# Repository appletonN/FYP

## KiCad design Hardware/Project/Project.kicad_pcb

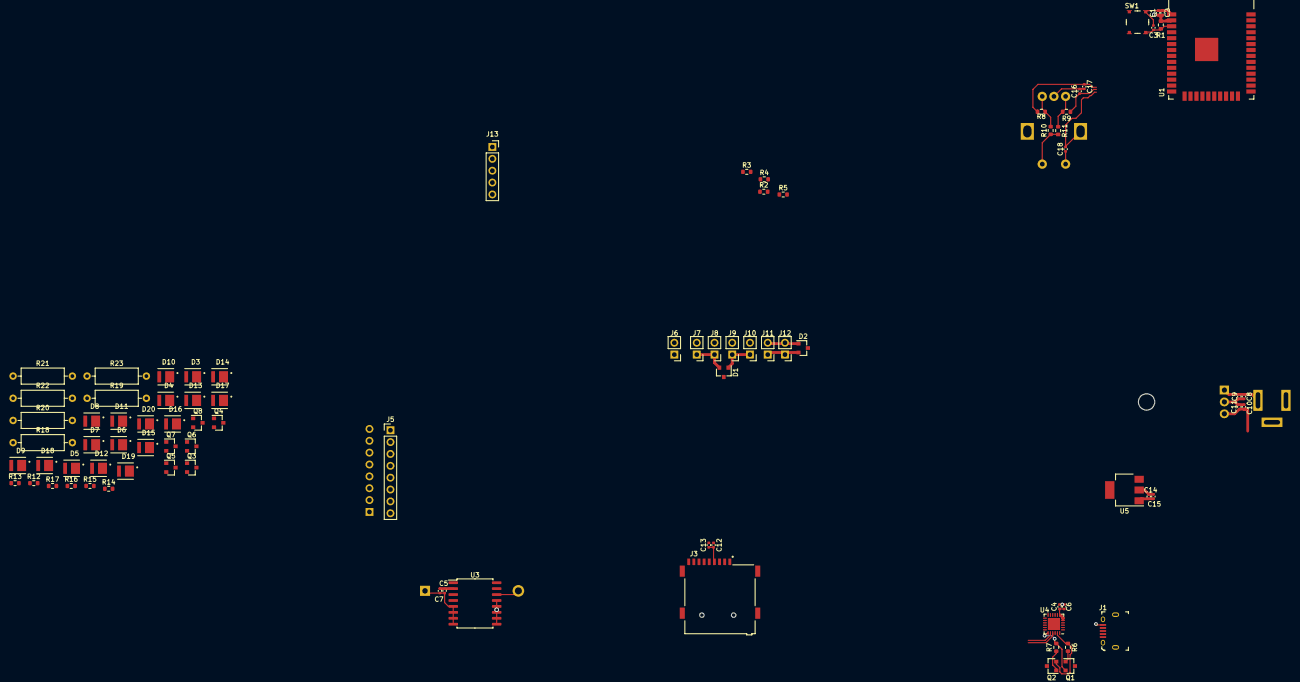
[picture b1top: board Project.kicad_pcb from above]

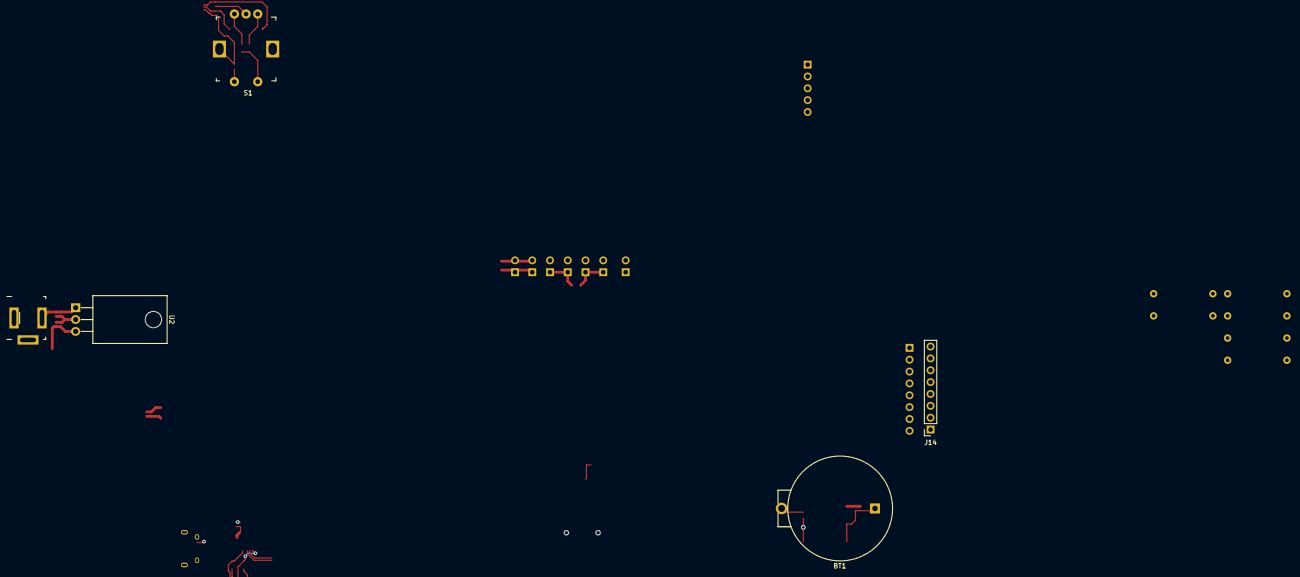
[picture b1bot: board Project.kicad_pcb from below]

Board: 4 copper layers, 90 parts (5 on the bottom side), 56 nets.

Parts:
BT1: Battery_Cell; Battery_Holder_Coin_2032_BS-7
C1, C4, C5, C12: 1n; C_0402_1005Metric
C2, C3, C6, C7, C9, C11, C13, C15: 100n; C_0402_1005Metric
C8, C10, C14: 4u7; C_0402_1005Metric
C16, C17, C18: 10n; C_0402_1005Metric
D1, D2: PSM712-LF-T7; SOT-23
D3, D4, D5, D6, D7, D8, D9, D10, D11, D12, D13, D14, D15, D16, D17, D18, D19, D20: LED; LED_L135-A589003500000
J1: USB_B_Micro; USB_Micro_B_Female_10118194-0001LF
J2: PJ-202-AH; Barrel_Jack_5.5mmODx2.1mmID_PJ-202A
J3: Micro_SD_Card_Det; GCT_MEM2075-00-140-01-A
J5: Conn_01x08_Male; PinHeader_1x08_P2.54mm_Vertical
J6, J7, J8, J9, J10, J11, J12: Conn_01x02; PinHeader_1x02_P2.54mm_Vertical
J13: Screen; PinSocket_1x05_P2.54mm_Vertical
J14: Conn_01x08_Male; PinSocket_1x08_P2.54mm_Vertical
Q1, Q2: MMBT3904; SOT-23
Q3, Q4, Q5, Q6, Q7, Q8: Q_PNP_BCE; SOT-23
R1, R2, R3, R4, R5, R6, R7, R8, R9, R10, R11: 10k; R_0603_1608Metric
R12, R13, R14, R15, R16, R17: 1k; R_0603_1608Metric
R18, R19, R20, R21, R22, R23: 180R; R_Axial_DIN0309_L9.0mm_D3.2mm_P12.70mm_Horizontal
S1: PEC11R-4020F-S0024; Rotary_Encoder_Switched_PEC11R
SW1: RESET; Switch_Tactile_SMD_4.5x4.5mm_TL3315NF160Q
U1: ESP32-WROOM-32
U2: LM7812_TO220; TO-220-3_Horizontal_TabDown
U3: DS3231M; SOIC-16W_7.5x10.3mm_P1.27mm
U4: CP2104; QFN-24-1EP_4x4mm_P0.5mm_EP2.6x2.6mm
U5: AMS1117-3.3; SOT-223-3_TabPin2

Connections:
+3V3: C1.1, C2.1, C4.1, C5.1, C6.1, C7.1, C12.1, C13.1, C14.1, C15.1, D1.2, J3.4, J7.1, J8.1, J13.1, J13.2, R1.2, R2.2, R3.2, R4.2, R5.2, R10.1, R11.1, S1.1, U1.2, U3.2, U4.5, U4.6, U4.7, U5.2
+12V: C10.1, C11.1, D1.1, J5.1, J9.1, J10.1, J14.8, R18.2, R19.2, R20.2, R21.2, R22.2, R23.2, U2.3, U5.3
/!SD_SS: J3.2, U1.24
/Button: C18.1, S1.2, U1.8
/EncoderA: C17.1, R8.1, U1.6
/EncoderB: C16.1, R9.1, U1.7
/IO0: Q2.3, U1.25
/OnOff: J6.1, U1.26
/PWM1: J5.7, J14.2, R12.1, U1.14
/PWM2: J5.6, J14.3, R13.1, U1.16
/PWM3: J5.5, J14.4, R14.1, U1.13
/PWM4: J5.4, J14.5, R15.1, U1.10
/PWM5: J5.3, J14.6, R16.1, U1.11
/PWM6: J5.2, J14.7, R17.1, U1.12
/RESET: C3.1, Q1.3, R1.1, SW1.2, U1.3
/RTC-32kHz: R3.1, U1.27, U3.1
/RTC-INTSQW: R2.1, U1.23, U3.3
/RTC-RST: U1.28, U3.4
/SD_Det: J3.9, U1.9
Earth: BT1.2, C1.2, C2.2, C3.2, C4.2, C5.2, C6.2, C7.2, C8.2, C9.2, C10.2, C11.2, C12.2, C13.2, C14.2, C15.2, C16.2, C17.2, C18.2, D1.3, D2.3, J1.5, J2.2, J3.6, J5.8, J6.2, J7.2, J8.2, J9.2, J10.2, J13.3, J14.1, Q3.2, Q4.2, Q5.2, Q6.2, Q7.2, Q8.2, S1.3, S1.C, SW1.1, U1.1, U1.15, U1.38, U1.39, U2.2, U3.5, U3.6, U3.7, U3.8, U3.9, U3.10, U3.11, U3.12, U3.13, U4.2, U4.25, U5.1
LINE: C8.1, C9.1, J2.1, U2.1
MISO: J3.7, U1.37
MOSI: J3.3, U1.31
unnamed: BT1.1, U3.14
unnamed: D3.1, D4.1, D5.1, Q3.3
unnamed: D3.2, D4.2, D5.2, R18.1
unnamed: D6.1, D7.1, D8.1, Q4.3
unnamed: D6.2, D7.2, D8.2, R19.1
unnamed: D9.1, D10.1, D11.1, Q5.3
unnamed: D9.2, D10.2, D11.2, R20.1
unnamed: D12.1, D13.1, D14.1, Q6.3
unnamed: D12.2, D13.2, D14.2, R21.1
unnamed: D15.1, D16.1, D17.1, Q7.3
unnamed: D15.2, D16.2, D17.2, R22.1
unnamed: D18.1, D19.1, D20.1, Q8.3
unnamed: D18.2, D19.2, D20.2, R23.1
unnamed: J1.1, U4.8
unnamed: J1.2, U4.4
unnamed: J1.3, U4.3
unnamed: Q1.1, R6.2
unnamed: Q1.2, R7.1, U4.19
unnamed: Q2.1, R7.2
unnamed: Q2.2, R6.1, U4.23
unnamed: Q3.1, R12.2
unnamed: Q4.1, R13.2
unnamed: Q5.1, R14.2
unnamed: Q6.1, R15.2
unnamed: Q7.1, R16.2
unnamed: Q8.1, R17.2
unnamed: R8.2, R10.2, S1.A
unnamed: R9.2, R11.2, S1.B
RXD: U1.34, U4.20
SCK: J3.5, U1.30
SCL: D2.2, J11.1, J12.1, J13.5, R5.1, U1.36, U3.16
SDA: D2.1, J11.2, J12.2, J13.4, R4.1, U1.33, U3.15
TXD: U1.35, U4.21

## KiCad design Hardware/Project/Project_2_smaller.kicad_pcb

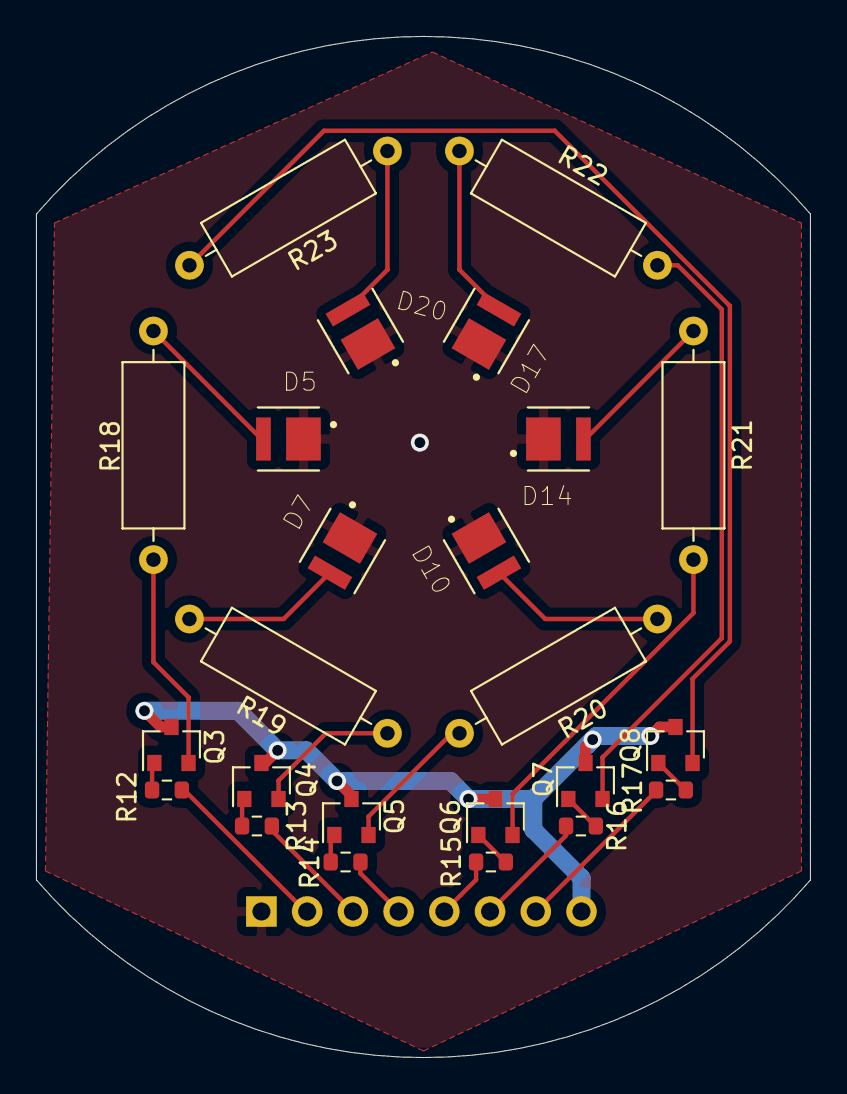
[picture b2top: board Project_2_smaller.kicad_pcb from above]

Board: 4 copper layers, 43.0 x 56.7 mm, 25 parts (1 on the bottom side), 26 nets.

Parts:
D5, D7, D10, D14, D17, D20: LED; LED_L135-A589003500000
J14: Conn_01x08_Male; PinSocket_1x08_P2.54mm_Vertical
Q3, Q4, Q5, Q6, Q7, Q8: Q_PNP_BCE; SOT-23
R12, R13, R14, R15, R16, R17: 1k; R_0603_1608Metric
R18, R19, R20, R21, R22, R23: 180R; R_Axial_DIN0309_L9.0mm_D3.2mm_P12.70mm_Horizontal

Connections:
+12V: J14.8, Q3.3, Q4.3, Q5.3, Q6.3, Q7.3, Q8.3
/PWM1: J14.2, R12.1
/PWM2: J14.3, R13.1
/PWM3: J14.4, R14.1
/PWM4: J14.5, R15.1
/PWM5: J14.6, R16.1
/PWM6: J14.7, R17.1
Earth: D5.1, D7.1, D10.1, D14.1, D17.1, D20.1, J14.1
unnamed: D5.2, R18.1
unnamed: D7.2, R19.1
unnamed: D10.2, R20.1
unnamed: D14.2, R21.1
unnamed: D17.2, R22.1
unnamed: D20.2, R23.1
unnamed: Q3.1, R12.2
unnamed: Q3.2, R18.2
unnamed: Q4.1, R13.2
unnamed: Q4.2, R19.2
unnamed: Q5.1, R14.2
unnamed: Q5.2, R20.2
unnamed: Q6.1, R15.2
unnamed: Q6.2, R21.2
unnamed: Q7.1, R16.2
unnamed: Q7.2, R22.2
unnamed: Q8.1, R17.2
unnamed: Q8.2, R23.2

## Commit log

2021-03-07 added ignore
2021-03-21 update 21-03-21
2021-04-08 First 2 Chapters
2021-04-20 added first part of methodology
2021-04-21 finished Methodology
2021-04-27 finished Conclusion
